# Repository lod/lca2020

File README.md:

# LCA2020 Tutorial - Kicad for Software Engineers

This project contains the slides, handout and supporting files for a tutorial to be delivered at LCA202 at the Gold Coast.

https://linux.conf.au/schedule/presentation/43/

The progress checkpoint files are in the electronics directory.

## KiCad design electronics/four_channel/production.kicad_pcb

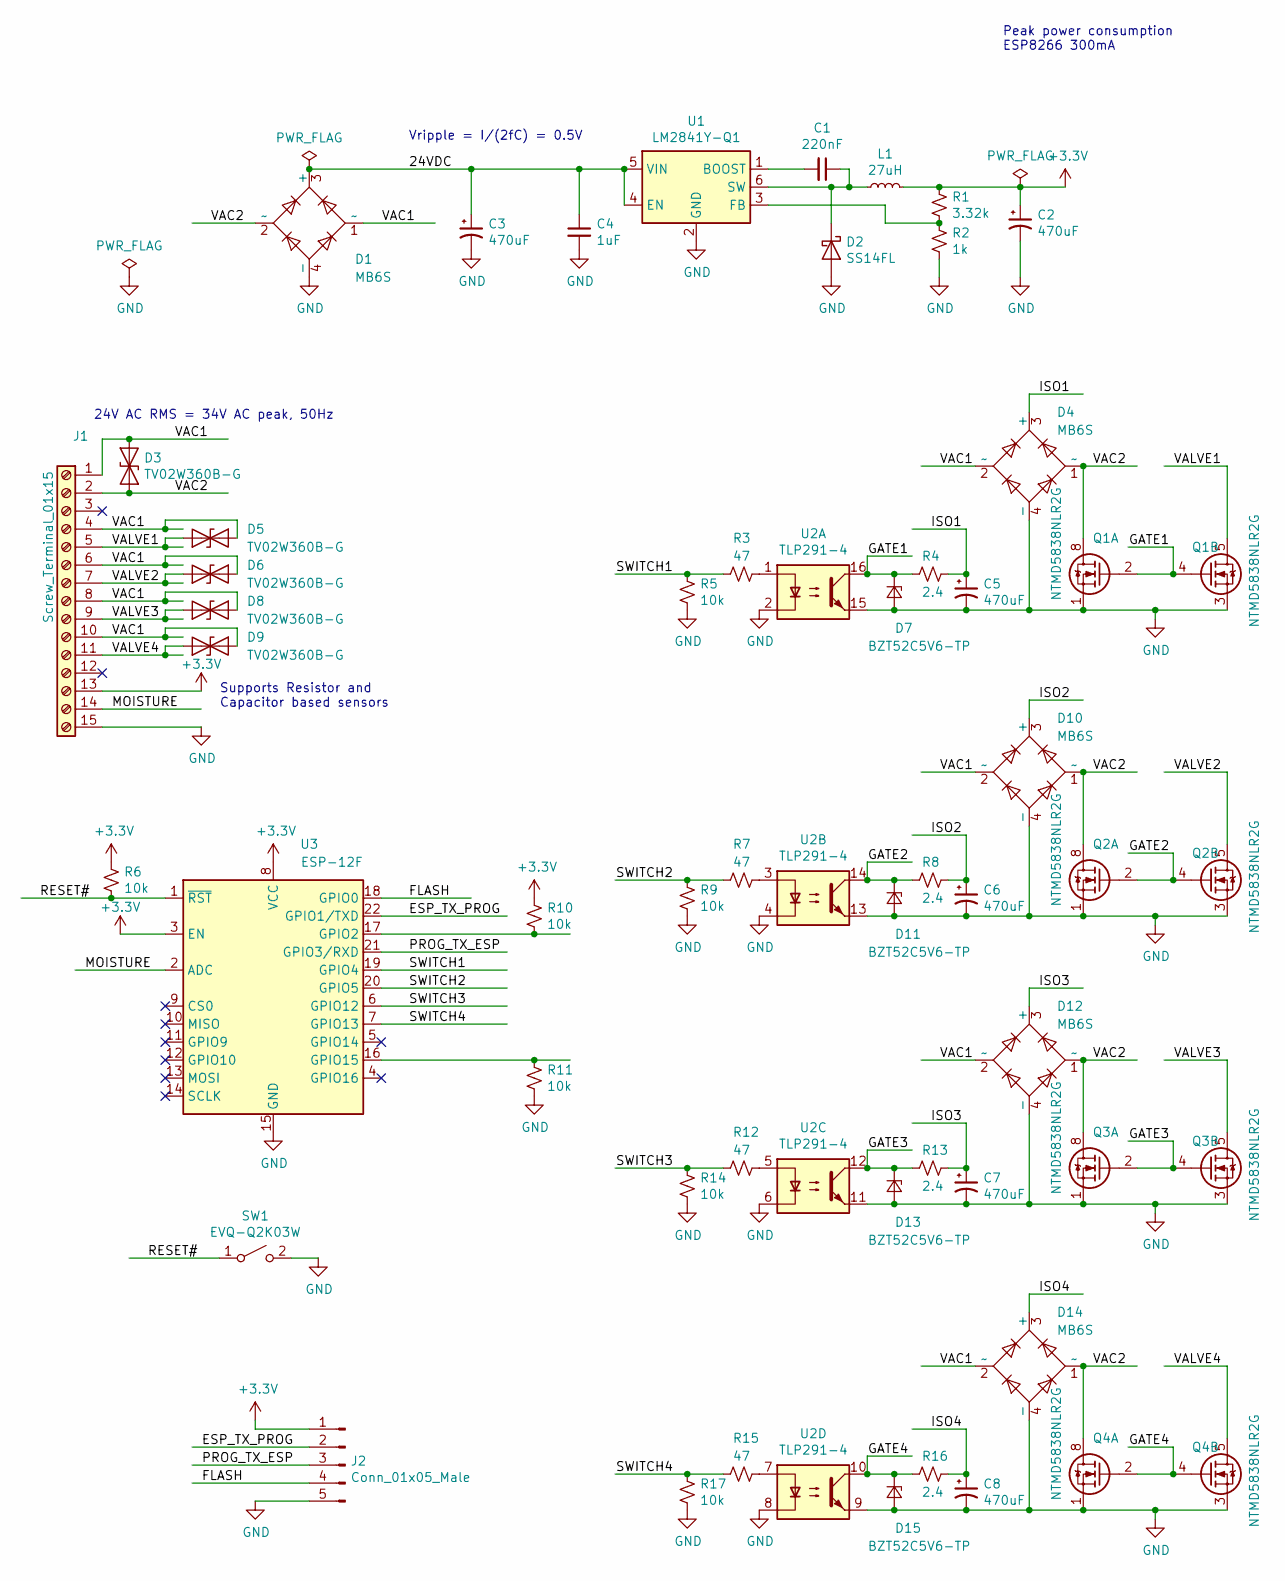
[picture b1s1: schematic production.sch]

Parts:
C1: 220nF; C_0603_1608Metric
C2, C3, C5, C6, C7, C8: 470uF; CP_Radial_D12.5mm_P5.00mm; Manufacturer Part Number EEU-FM1H471
C4: 1uF; C_0603_1608Metric
D1, D4, D10, D12, D14: MB6S; TO-269AA
D2: SS14FL; D_SOD-123F
D3, D5, D6, D8, D9: TV02W360B-G; D_SOD-123
D7, D11, D13, D15: BZT52C5V6-TP; D_SOD-123
J1: Screw_Terminal_01x15; TerminalBlock_Phoenix_PT-1,5-15-5.0-H_1x15_P5.00mm_Horizont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
J2: Conn_01x05_Male; PinHeader_1x05_P1.27mm_Vertical
L1: 27uH; L_0805_2012Metric
Q1, Q2, Q3, Q4: NTMD5838NLR2G; SOIC-8_3.9x4.9mm_P1.27mm
R1: 3.32k; R_0603_1608Metric
R2: 1k; R_0603_1608Metric
R3, R7, R12, R15: 47; R_0603_1608Metric
R4, R8, R13, R16: 2.4; R_0603_1608Metric
R5, R6, R9, R10, R11, R14, R17: 10k; R_0603_1608Metric
SW1: EVQ-Q2K03W; SW_SPST_EVQQ2
U1: LM2841Y-Q1; TSOT-23-6
U2: TLP291-4; SOIC-16_4.55x10.3mm_P1.27mm
U3: ESP-12F; ESP-12E

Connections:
+3V3: C2.1, J1.13, J2.1, L1.2, R1.1, R6.1, R10.2, U3.3 (EN), U3.8 (VCC)
/24VDC: C3.1, C4.1, D1.3 (+), U1.4 (EN), U1.5 (VIN)
/ESP_TX_PROG: J2.2, U3.22 (GPIO1/TXD)
/FLASH: J2.4, U3.18 (GPIO0)
/GATE1: D7.1 (K), Q1.2 (G1), Q1.4 (G2), R4.2, U2.16
/GATE2: D11.1 (K), Q2.2 (G1), Q2.4 (G2), R8.2, U2.14
/GATE3: D13.1 (K), Q3.2 (G1), Q3.4 (G2), R13.2, U2.12
/GATE4: D15.1 (K), Q4.2 (G1), Q4.4 (G2), R16.2, U2.10
/ISO1: C5.1, D4.3 (+), R4.1
/ISO2: C6.1, D10.3 (+), R8.1
/ISO3: C7.1, D12.3 (+), R13.1
/ISO4: C8.1, D14.3 (+), R16.1
/MOISTURE: J1.14, U3.2 (ADC)
/PROG_TX_ESP: J2.3, U3.21 (GPIO3/RXD)
/RESET#: R6.2, SW1.1 (A), U3.1 (~RST)
/SWITCH1: R3.2, R5.1, U3.19 (GPIO4)
/SWITCH2: R7.2, R9.1, U3.20 (GPIO5)
/SWITCH3: R12.2, R14.1, U3.6 (GPIO12)
/SWITCH4: R15.2, R17.1, U3.7 (GPIO13)
/VAC1: D1.1 (~~), D3.1 (A1), D4.2 (~~), D5.2 (A2), D6.2 (A2), D8.2 (A2), D9.2 (A2), D10.2 (~~), D12.2 (~~), D14.2 (~~), J1.1, J1.4, J1.6, J1.8, J1.10
/VAC2: D1.2 (~~), D3.2 (A2), D4.1 (~~), D10.1 (~~), D12.1 (~~), D14.1 (~~), J1.2, Q1.7 (D1), Q1.8 (D1), Q2.7 (D1), Q2.8 (D1), Q3.7 (D1), Q3.8 (D1), Q4.7 (D1), Q4.8 (D1)
/VALVE1: D5.1 (A1), J1.5, Q1.5 (D2), Q1.6 (D2)
/VALVE2: D6.1 (A1), J1.7, Q2.5 (D2), Q2.6 (D2)
/VALVE3: D8.1 (A1), J1.9, Q3.5 (D2), Q3.6 (D2)
/VALVE4: D9.1 (A1), J1.11, Q4.5 (D2), Q4.6 (D2)
GND: C2.2, C3.2, C4.2, C5.2, C6.2, C7.2, C8.2, D1.4 (-), D2.2 (A), D4.4 (-), D7.2 (A), D10.4 (-), D11.2 (A), D12.4 (-), D13.2 (A), D14.4 (-), D15.2 (A), J1.15, J2.5, Q1.1 (S1), Q1.3 (S2), Q2.1 (S1), Q2.3 (S2), Q3.1 (S1), Q3.3 (S2), Q4.1 (S1), Q4.3 (S2), R2.2, R5.2, R9.2, R11.2, R14.2, R17.2, SW1.2 (B), U1.2 (GND), U2.2, U2.4, U2.6, U2.8, U2.9, U2.11, U2.13, U2.15, U3.15 (GND)
unnamed: C1.1, D2.1 (K), L1.1, U1.6 (SW)
unnamed: C1.2, U1.1 (BOOST)
unnamed: R1.2, R2.1, U1.3 (FB)
unnamed: R3.1, U2.1
unnamed: R7.1, U2.3
unnamed: R10.1, U3.17 (GPIO2)
unnamed: R11.1, U3.16 (GPIO15)
unnamed: R12.1, U2.5
unnamed: R15.1, U2.7

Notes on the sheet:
Peak power consumption ESP8266 300mA
Vripple = I/(2fC) = 0.5V
24V AC RMS = 34V AC peak, 50Hz
Supports Resistor and Capacitor based sensors

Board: 2 copper layers, 51 parts (0 on the bottom side), 35 nets, no tracks yet.

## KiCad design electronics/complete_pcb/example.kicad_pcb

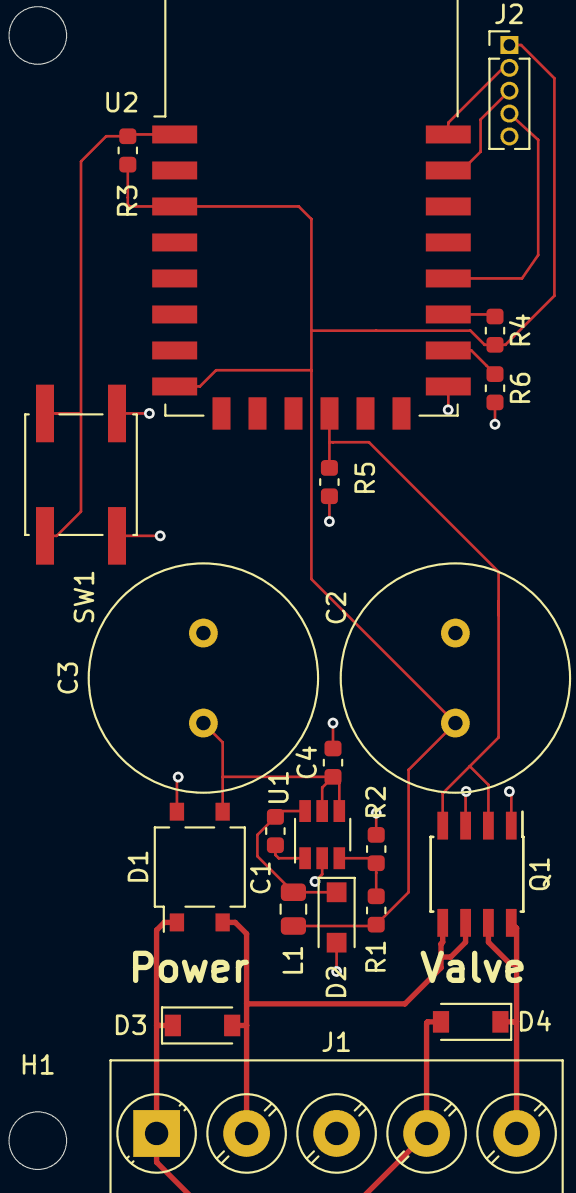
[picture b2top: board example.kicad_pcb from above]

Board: 2 copper layers, 25 parts (0 on the bottom side), 16 nets.

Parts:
C1: 220nF; C_0603_1608Metric
C2, C3: 470uF; C_Radial_D12.5mm_H20.0mm_P5.00mm
C4: 1uF; C_0603_1608Metric
D1: MB6S; TO-269AA
D2: SS14FL; D_SOD-123F
D3, D4: TV02W360B-G; D_SOD-123
H1, H2, H3, H4: MountingHole; MountingHole_3.2mm_M3
J1: Screw_Terminal_01x05; TerminalBlock_Phoenix_PT-1,5-5-5.0-H_1x05_P5.00mm_Horizontal
J2: Conn_01x05_Male; PinHeader_1x05_P1.27mm_Vertical
L1: 27uH; L_0805_2012Metric
Q1: NTMD5838NLR2G; SOIC-8_3.9x4.9mm_P1.27mm
R1: 3.32k; R_0603_1608Metric
R2: 1k; R_0603_1608Metric
R3, R4, R5, R6: 10k; R_0603_1608Metric
SW1: EVQ-Q2K03W; SW_SPST_EVQQ2
U1: LM2841Y-Q1; TSOT-23-6
U2: ESP-12F; ESP-12E

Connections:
+3V3: C2.1, J2.1, L1.2, R1.1, R3.1, R4.2, U2.3, U2.8
/24VDC: C3.1, C4.1, D1.3, U1.4, U1.5
/ESP_TX_PROG: J2.2, U2.22
/FLASH: J2.4, U2.18
/PROG_TX_ESP: J2.3, U2.21
/RESET#: R3.2, SW1.1, U2.1
/SWITCH1: Q1.2, Q1.4, R5.1, U2.12
/VAC1: D1.1, D3.1, D4.2, J1.1, J1.4
/VAC2: D1.2, D3.2, J1.2, Q1.5, Q1.6
/VALVE1: D4.1, J1.5, Q1.7, Q1.8
GND: C2.2, C3.2, C4.2, D1.4, D2.2, J2.5, Q1.1, Q1.3, R2.2, R5.2, R6.2, SW1.2, U1.2, U2.15
unnamed: C1.1, D2.1, L1.1, U1.6
unnamed: C1.2, U1.1
unnamed: R1.2, R2.1, U1.3
unnamed: R4.1, U2.17
unnamed: R6.1, U2.16

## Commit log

2020-01-14 Initial backup
2020-01-15 Updated slides
    Tweaks to work at the presenting resolution
    Tweaks to styling
2020-01-15 Clean up / restructure electronics files
2020-01-15 Basic readme
